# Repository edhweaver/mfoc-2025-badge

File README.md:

# mfoc-2025-badge

This repo contains the Design Files and supporting documentation for the Maker Faire Orange County 2025 Badge.
* maker-faire-badge.kicad_pro - KiCad Project File
* maker-faire-badge.kicad_prb - KiCad Layout File
* maker-faire-badge.kicad_sch - KiCad Schematic File
* Library.pretty\ - contains all footprints artwork
* Manufacturing Files
  * PCB-maker-faire-badge-Rev_X.zip - Printed Circuit Board Artwork and Fabrication Files
  * ASSEMBLY-maker-faire-badge-Rev_X.zip - PCB Assembly Files (Bill of Materials and Assembly Documentation)
* README.mk - this file
* CHANGES.txt - Change log of modifications from prior published design as required by the CERN-OHL-S license
* cern_ohl_s_v2_user_guide.txt - User Guide for the CERN-OHL-S license
* LICENSES\ - contains all project licenses

## License Information

The MFOC 2025 Badge hardware and all documentation in this repository are licensed under the CERN Open Hardware License, strongly reciprocal, v2.0 or later (CERN-OHL-S-2.0).

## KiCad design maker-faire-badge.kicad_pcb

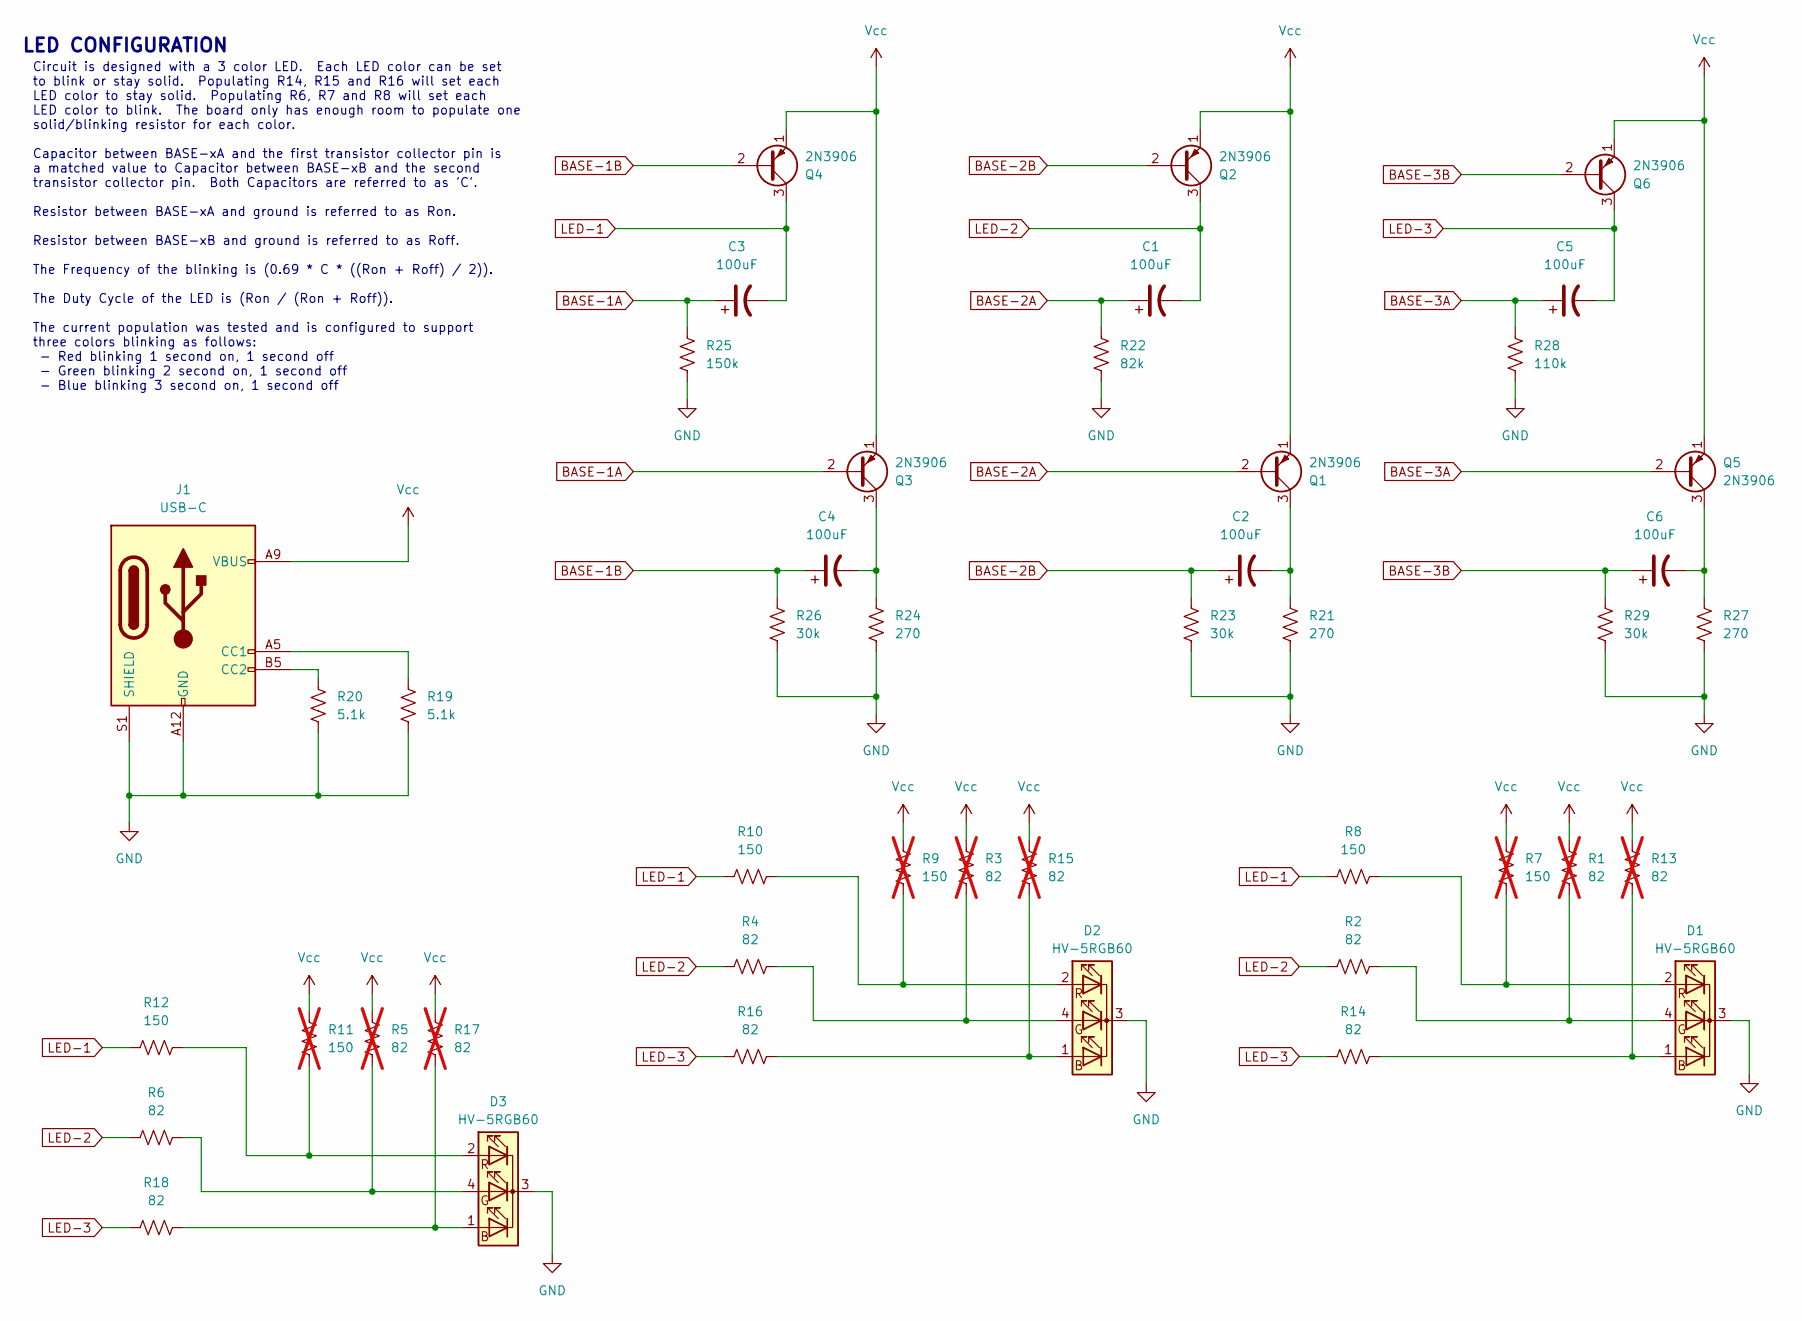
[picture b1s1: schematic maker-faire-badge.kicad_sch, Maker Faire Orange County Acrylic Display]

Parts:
C1, C2, C3, C4, C5, C6: 100uF; CP_Radial_D5.0mm_P2.50mm; PartNumber ECA-1CM101I
D1, D2, D3: HV-5RGB60; LED_D5.0mm-4_RGB_Wide_Pins; PartNumber HV-5RGB60
J1: USB-C; USB_C_Receptacle_GCT_USB4135-GF-A_6P_TopMnt_Horizontal; PartNumber 10174819-00011LF
Q1, Q2, Q3, Q4, Q5, Q6: 2N3906; TO-92_Inline_Wide; PartNumber 2N3906TFR
R1, R3, R5, R13, R15, R17: 82; R_Axial_DIN0207_L6.3mm_D2.5mm_P2.54mm_Vertical; PartNumber CFR-25JB-52-82R; not fitted
R2, R4, R6, R14, R16, R18: 82; R_Axial_DIN0207_L6.3mm_D2.5mm_P2.54mm_Vertical; PartNumber CFR-25JB-52-82R
R7, R9, R11: 150; R_Axial_DIN0207_L6.3mm_D2.5mm_P2.54mm_Vertical; PartNumber CFR-25JB-52-150R; not fitted
R8, R10, R12: 150; R_Axial_DIN0207_L6.3mm_D2.5mm_P2.54mm_Vertical; PartNumber CFR-25JB-52-150R
R19, R20: 5.1k; R_Axial_DIN0207_L6.3mm_D2.5mm_P2.54mm_Vertical; PartNumber CFR-25JB-52-5K1
R21, R24, R27: 270; R_Axial_DIN0207_L6.3mm_D2.5mm_P2.54mm_Vertical; PartNumber CFR-25JB-52-270R
R22: 82k; R_Axial_DIN0207_L6.3mm_D2.5mm_P2.54mm_Vertical; PartNumber CFR-25JB-52-82k
R23, R26, R29: 30k; R_Axial_DIN0207_L6.3mm_D2.5mm_P2.54mm_Vertical; PartNumber CFR-25JB-52-30K
R25: 150k; R_Axial_DIN0207_L6.3mm_D2.5mm_P2.54mm_Vertical; PartNumber CFR-25JB-52-150K
R28: 110k; R_Axial_DIN0207_L6.3mm_D2.5mm_P2.54mm_Vertical; PartNumber CFR-25JB-52-110K

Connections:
BASE-1A: C3.1, Q3.2 (B), R25.2
BASE-1B: C4.1, Q4.2 (B), R26.2
BASE-2A: C1.1, Q1.2 (B), R22.2
BASE-2B: C2.1, Q2.2 (B), R23.2
BASE-3A: C5.1, Q5.2 (B), R28.2
BASE-3B: C6.1, Q6.2 (B), R29.2
GND: D1.3 (K), D2.3 (K), D3.3 (K), J1.A12 (GND), J1.B12 (GND), J1.S1 (SHIELD), R19.1, R20.1, R21.1, R22.1, R23.1, R24.1, R25.1, R26.1, R27.1, R28.1, R29.1
LED-1: C3.2, Q4.3 (C), R8.2, R10.2, R12.2
LED-2: C1.2, Q2.3 (C), R2.2, R4.2, R6.2
LED-3: C5.2, Q6.3 (C), R14.2, R16.2, R18.2
unnamed: D1.1 (BA), R13.1, R14.1
unnamed: D1.4 (GA), R1.1, R2.1
unnamed: D1.2 (RA), R7.1, R8.1
unnamed: D2.1 (BA), R15.1, R16.1
unnamed: D2.4 (GA), R3.1, R4.1
unnamed: D2.2 (RA), R9.1, R10.1
unnamed: D3.1 (BA), R17.1, R18.1
unnamed: D3.4 (GA), R5.1, R6.1
unnamed: D3.2 (RA), R11.1, R12.1
unnamed: J1.A5 (CC1), R19.2
unnamed: J1.B5 (CC2), R20.2
unnamed: C2.2, Q1.3 (C), R21.2
unnamed: C4.2, Q3.3 (C), R24.2
unnamed: C6.2, Q5.3 (C), R27.2
Vcc: J1.A9 (VBUS), J1.B9 (VBUS), Q1.1 (E), Q2.1 (E), Q3.1 (E), Q4.1 (E), Q5.1 (E), Q6.1 (E), R1.2, R3.2, R5.2, R7.2, R9.2, R11.2, R13.2, R15.2, R17.2

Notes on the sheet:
Circuit is designed with a 3 color LED. Each LED color can be set to blink or stay solid. Populating R14, R15 and R16 will set each LED color to stay solid. Populating R6, R7 and R8 will set each LED color to blink. The board only has enough room to populate one solid/blinking resistor for each col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
LED CONFIGURATION

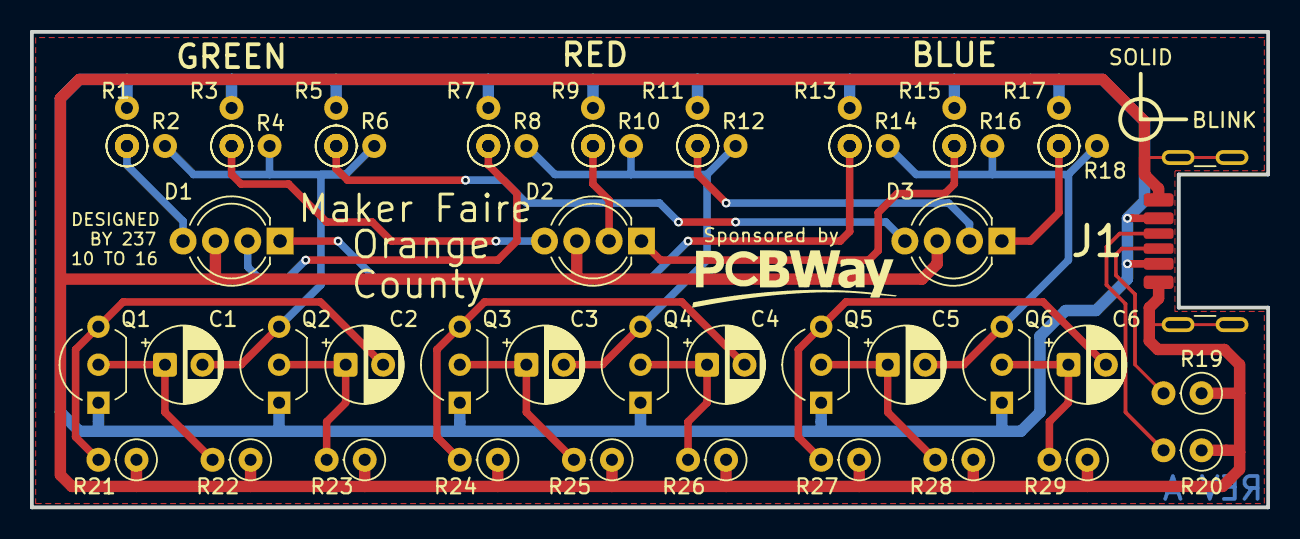
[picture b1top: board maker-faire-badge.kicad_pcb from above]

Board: 2 copper layers, 82.6 x 31.7 mm, 45 parts (0 on the bottom side), 25 nets.

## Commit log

2025-10-26 Add manufacturer files
2025-10-26 User/ed cleanup (#1)
    * Added Design files for Revision A
    * Add Manufacturer files for Revision A
    * Added License information
2025-10-26 Updated Library components
2025-10-26 updated design files
2025-10-26 fixed title block
2025-10-26 Added manufacturing files
2025-10-26 updated changes.txt
2025-10-26 fixed layout title block
2025-10-26 embedded title block in layout
2025-10-26 User/ed cleanup (#2)
    * Updated Library components
    * Updated Silkscreen on Layout
    * Added manufacturing files
2025-10-26 Update README.md
    Updated Readme to include all project file information.
2025-10-26 Updated Change Log
2025-10-26 updated schematic title block
2025-10-26 new manufacturing informaiton
2025-10-27 updated Assembly zip to include all documentation
2025-10-27 MFOC 2025 Boards - Revision C
    * Updated Change Log
    * Updated Change Log
    * Added Manufacturing Files
    * updated design files
    * updated schematic title block
    * new manufacturing informaiton
2025-11-14 Initial design if Acylic Display PCBA
2026-01-02 BOM and Fabrication Note corrections
